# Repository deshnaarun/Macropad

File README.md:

# Macropad v1

A 4-key macropad with a rotary encoder and OLED display 

I started this project as a way to experiment with hardware. 

## Features

- 4 Cherry MX-style mechanical switches
- Rotary encoder with push-button (volume up/down + mute by default)
- 0.91" 128x32 SSD1306 OLED display showing a pixel-art cat that reacts to typing speed (sleeps when idle, walks at normal pace, runs when typed quickly)
- Custom 3D-printed two-part case (base + lid)

## CAD Model
The case is two printed parts with a base that holds the PCB and a lid that screws on top. 
Made in Fusion360

## PCB 
Made in KiCad. It's a 2 layer board, 80 X 84 mm. Each switch goes to its own key matrix, no diodes.
Schematic: 
PCB:

## Firmware

The encoder controls volume level. Press to mute.
The 4 keys are placeholders right now but I will set them up to use my most frequent apps (Still experimenting with this but building the case would help me better with this)
The OLED displays a cat. 

## BOM

4x Cherry MX-style switches 
4x 1u MX keycaps 
1x EC11 rotary encoder with push switch 
* 1x Encoder knob 
*  1x 0.91" 128x32 SSD1306 I2C OLED (pin order GND-VCC-SCL-SDA) 
*   1x Seeed XIAO RP2040 
*   4x M3 screws 
*   1x PCB 
*   1x Case (2 printed parts: body + lid)

## Repo structure

- **`cad/`** — Complete assembled 3D model of the case + PCB (STEP)
- **`pcb/`** — KiCad schematic and PCB design source files
- **`firmware/`** — QMK firmware source (keymap, config, OLED animation)
- **`production/`** — Ready-to-manufacture/flash files: Gerbers, individual case part STEPs, and compiled `firmware.uf2`

MIT — see [LICENSE](LICENSE).

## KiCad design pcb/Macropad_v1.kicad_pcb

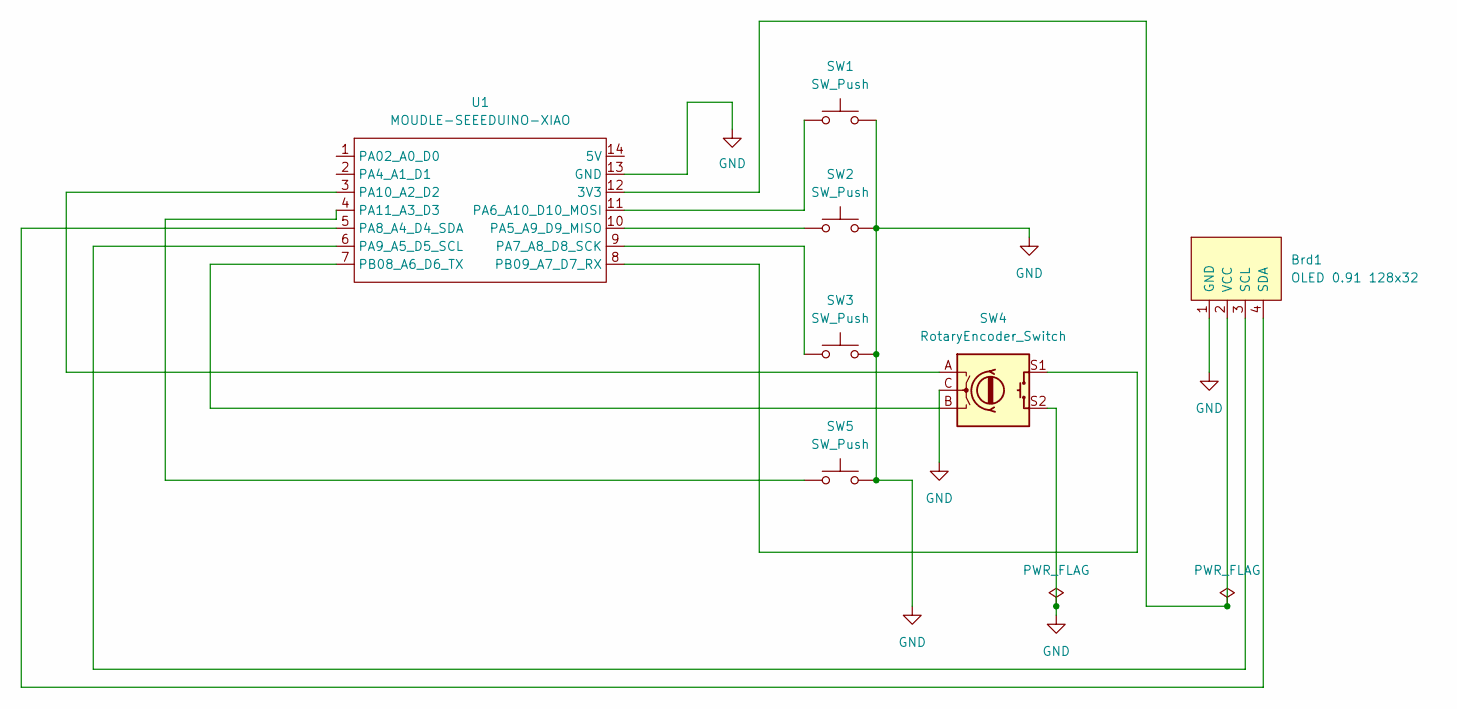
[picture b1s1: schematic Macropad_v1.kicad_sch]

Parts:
Brd1: OLED 0.91 128x32; PinHeader_1x04_P2.54mm_Vertical
SW1, SW2, SW3, SW5: SW_Push; SW_Cherry_MX_1.00u_PCB
SW4: RotaryEncoder_Switch; RotaryEncoder_Alps_EC11E-Switch_Vertical_H20mm
U1: MOUDLE-SEEEDUINO-XIAO; XIAO-Generic-Hybrid-14P-2.54-21X17.8MM

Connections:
GND: Brd1.1 (GND), SW1.2, SW2.2, SW3.2, SW4.C, SW4.S2, SW5.2, U1.13 (GND)
unnamed: Brd1.3 (SCL), U1.6 (PA9_A5_D5_SCL)
unnamed: Brd1.4 (SDA), U1.5 (PA8_A4_D4_SDA)
unnamed: Brd1.2 (VCC), U1.12 (3V3)
unnamed: SW2.1, U1.10 (PA5_A9_D9_MISO)
unnamed: SW1.1, U1.11 (PA6_A10_D10_MOSI)
unnamed: SW3.1, U1.9 (PA7_A8_D8_SCK)
unnamed: SW4.A, U1.3 (PA10_A2_D2)
unnamed: SW5.1, U1.4 (PA11_A3_D3)
unnamed: SW4.B, U1.7 (PB08_A6_D6_TX)
unnamed: SW4.S1, U1.8 (PB09_A7_D7_RX)

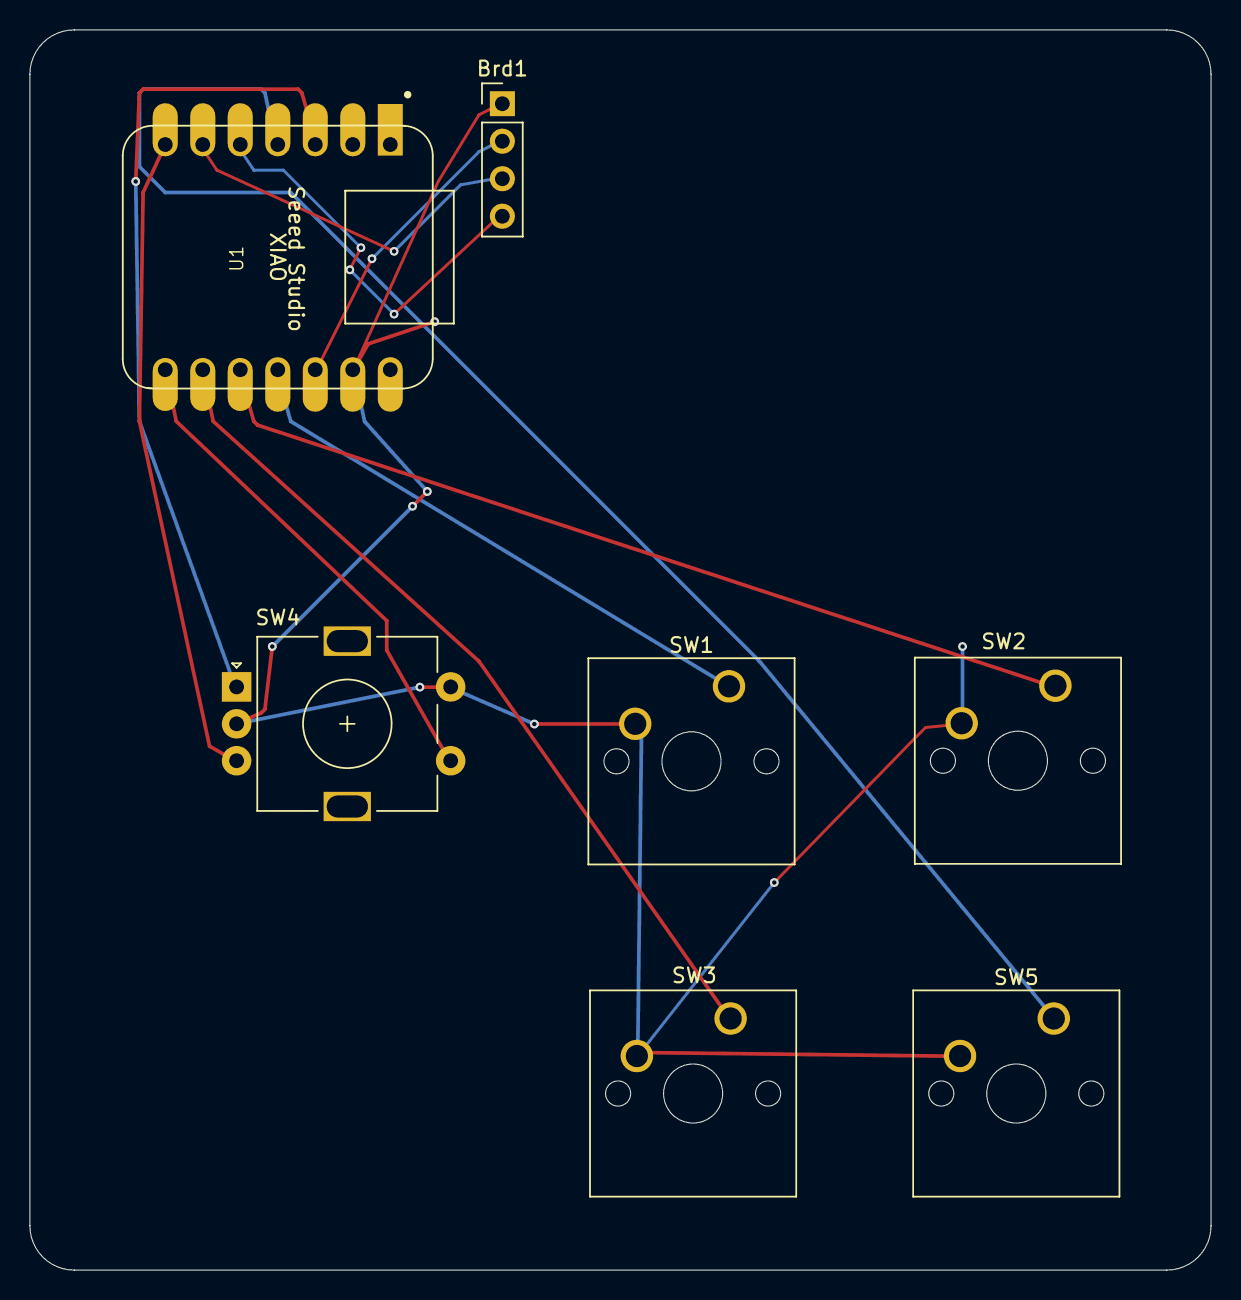
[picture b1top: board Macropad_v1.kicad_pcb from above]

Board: 2 copper layers, 80.0 x 84.0 mm, 7 parts (0 on the bottom side), 11 nets.
